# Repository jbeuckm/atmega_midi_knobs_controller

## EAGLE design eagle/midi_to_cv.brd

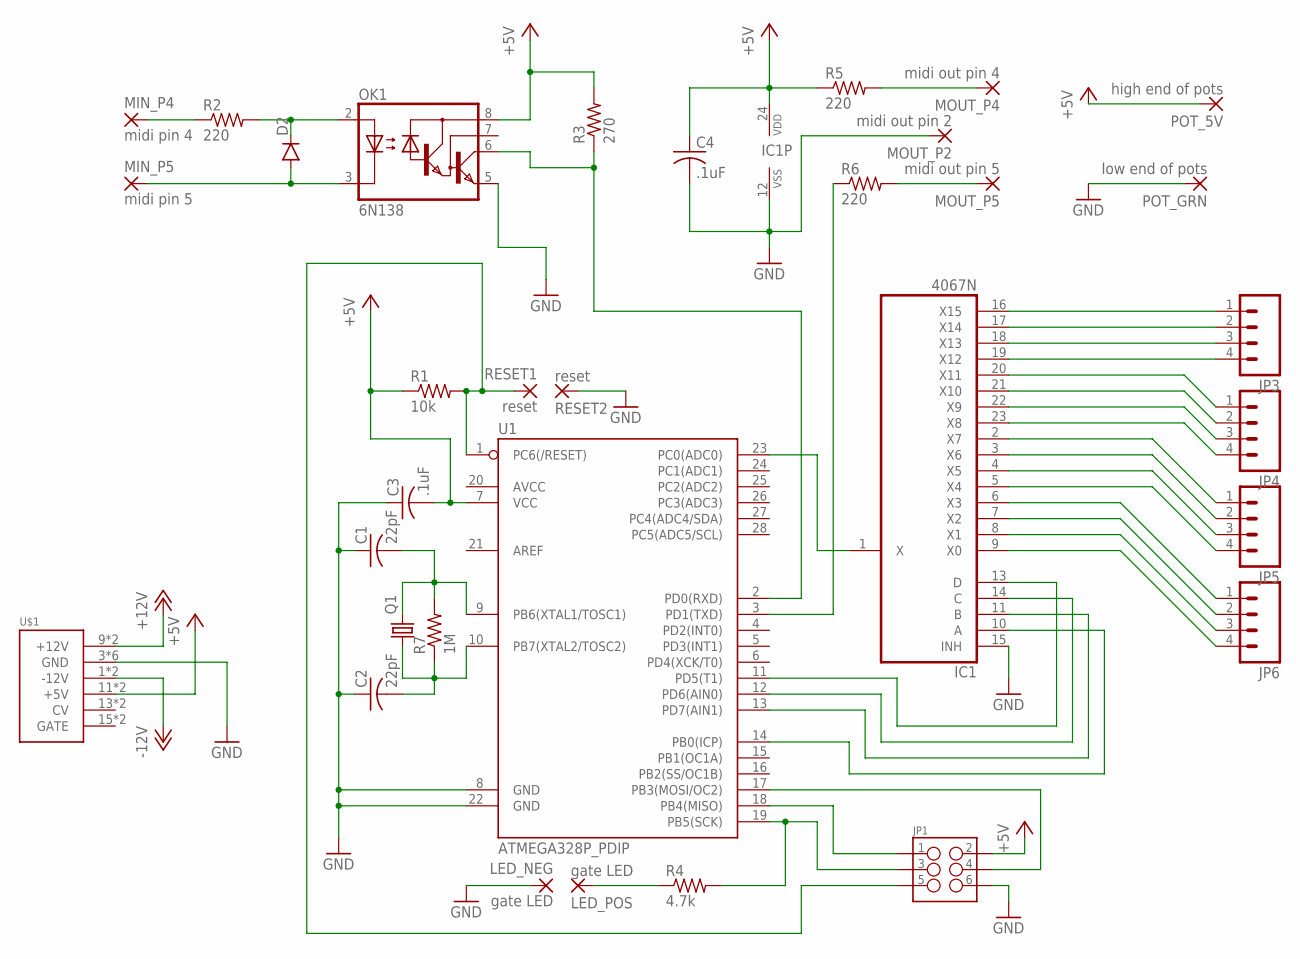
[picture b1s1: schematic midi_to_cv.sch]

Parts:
C1, C2: 22pF; C025-040X050
C3, C4: .1uF; C025-040X050
D2: DIODE1N4148; DIODE-1N4148
IC1: 4067N; DIL24-6
JP1: M03X2NO_SILK; 2X3-NS
JP3, JP4, JP5, JP6: M04LONGPADS; 1X04_LONGPADS
LED_NEG: gate LED; 2,54/0,9
LED_POS: gate LED; 2,54/0,9
MIN_P4: midi pin 4; 2,54/0,9
MIN_P5: midi pin 5; 2,54/0,9
MOUT_P2: midi out pin 2; 2,54/0,9
MOUT_P4: midi out pin 4; 2,54/0,9
MOUT_P5: midi out pin 5; 2,54/0,9
OK1: 6N138; DIL08
POT_5V: high end of pots; 2,54/0,9
POT_GRN: low end of pots; 2,54/0,9
Q1: CRYSTALHC49U-V; HC49U-V
R1: 10k; 0207/10
R2, R5, R6: 220; 0207/10
R3: 270; 0207/10
R4: 4.7k; 0207/10
R7: 1M; 0207/10
RESET1, RESET2: reset; 2,54/0,9
U1: ATMEGA328P_PDIP; DIL28-3
U$1: POWER; POWER_16

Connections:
+5V: C3.2, C4.1, IC1.24 (VDD), JP1.2, OK1.8 (VCC), POT_5V.1, R1.1, R3.2, R5.1, U1.7 (VCC), U$1.11 (+5V), U$1.12 (+5V)
+12V: U$1.9 (+12V), U$1.10 (+12V)
-12V: U$1.1 (-12V), U$1.2 (-12V)
GND: C1.1, C2.1, C3.1, C4.2, IC1.12 (VSS), IC1.15 (INH), JP1.6, LED_NEG.1, MOUT_P2.1, OK1.5 (GND), POT_GRN.1, RESET2.1, U1.8 (GND), U1.22 (GND), U$1.3 (GND), U$1.4 (GND), U$1.5 (GND), U$1.6 (GND), U$1.7 (GND), U$1.8 (GND)
unnamed: JP1.5, R1.2, RESET1.1, U1.1 (PC6(/RESET))
unnamed: IC1.9 (X0), JP6.4
unnamed: IC1.8 (X1), JP6.3
unnamed: C1.2, Q1.2, R7.2, U1.9 (PB6(XTAL1/TOSC1))
unnamed: C2.2, Q1.1, R7.1, U1.10 (PB7(XTAL2/TOSC2))
unnamed: MOUT_P5.1, R6.2
unnamed: IC1.7 (X2), JP6.2
unnamed: IC1.6 (X3), JP6.1
unnamed: IC1.13 (D), U1.11 (PD5(T1))
unnamed: JP1.3, R4.2, U1.19 (PB5(SCK))
unnamed: LED_POS.1, R4.1
unnamed: IC1.14 (C), U1.12 (PD6(AIN0))
unnamed: IC1.11 (B), U1.13 (PD7(AIN1))
unnamed: IC1.10 (A), U1.14 (PB0(ICP))
unnamed: IC1.5 (X4), JP5.4
unnamed: R6.1, U1.3 (PD1(TXD))
unnamed: IC1.4 (X5), JP5.3
unnamed: IC1.1 (X), U1.23 (PC0(ADC0))
unnamed: IC1.3 (X6), JP5.2
unnamed: IC1.2 (X7), JP5.1
unnamed: IC1.23 (X8), JP4.4
unnamed: IC1.22 (X9), JP4.3
unnamed: IC1.21 (X10), JP4.2
unnamed: IC1.20 (X11), JP4.1
unnamed: IC1.19 (X12), JP3.4
unnamed: IC1.18 (X13), JP3.3
unnamed: IC1.17 (X14), JP3.2
unnamed: IC1.16 (X15), JP3.1
unnamed: D2.A, MIN_P5.1, OK1.3 (C)
unnamed: D2.C, OK1.2 (A), R2.2
unnamed: MIN_P4.1, R2.1
unnamed: OK1.6 (VO), R3.1, U1.2 (PD0(RXD))
unnamed: MOUT_P4.1, R5.2
unnamed: JP1.4, U1.17 (PB3(MOSI/OC2))
unnamed: JP1.1, U1.18 (PB4(MISO))

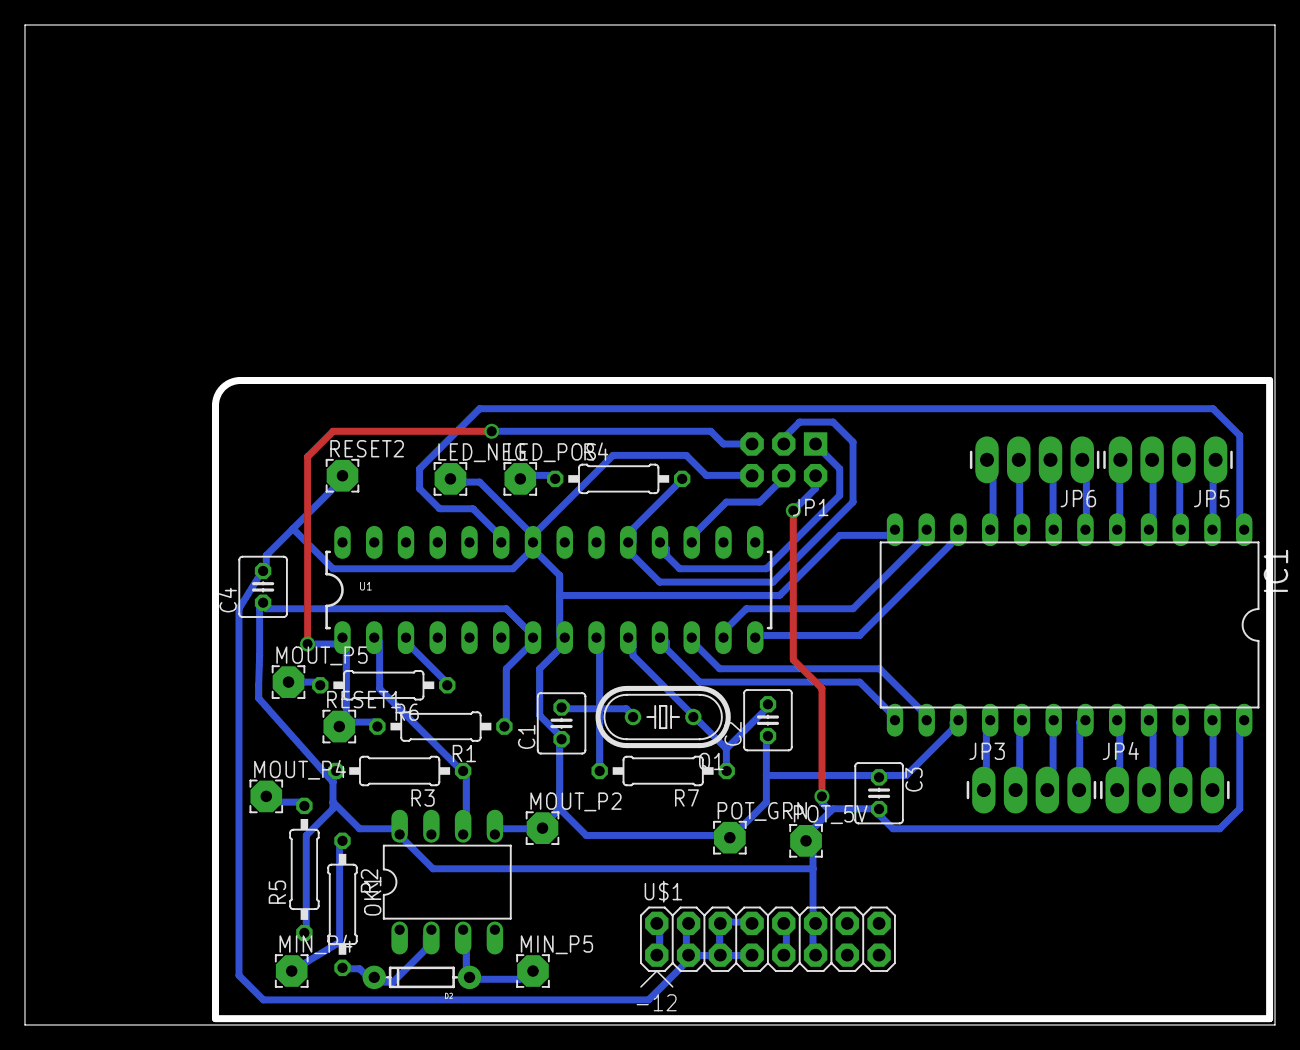
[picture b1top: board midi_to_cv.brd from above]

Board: 2 copper layers, 99.4 x 79.4 mm, 33 parts (0 on the bottom side), 39 nets.

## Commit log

2015-06-04 panel for resonant eq controller
2015-06-12 code working in hardware
2015-06-17 sending midi thru

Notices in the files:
parts and their libraries:
SparkFun-DigitalIC: Licensing: Creative Commons ShareAlike 4.0 International - https://creativecommons.org/licenses/by-sa/4.0
